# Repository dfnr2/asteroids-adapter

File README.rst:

Asteroids PCB -> Asteroids Deluxe Cabinet (and vice versa) Adapter
==================================================================

Background
----------

It is occasionally desirable to use an Asteroids PCB in an Asteroids Deluxe
cabinet (or vice versa). For example, the Braze Asteroids Multigame adapter
offers some advantages over the Asteroids Deluxe version of the multigame, such
as more accurate sound, and a Lunar Lander thruster interface. Or one may want
to use an Asteroids cabinet for testing both Asteroids and Asteroids Deluxe
PCBs. Or one may prefer the aesthetics of one cabinet, but the gameplay of the
other PCB.

The Asteroids PCB is almost compatible with the Asteroids Deluxe cabinet (and
vice versa). There are a few differences that must be addressed for an Asteroids
PCB to properly work in an Asteroids Deluxe cabinet:

#. The Deluxe cabinet uses a mirror to produce a floating 3D effect, which has the
   side effect of inverting the image along the Y axis, so Asteroids Y output needs
   to be inverted to properly work on an Asteroids Deluxe cabinet.

#. The Y-axis flip is only true for full standup cabinets. An Asteroids in an
   Asteroids Deluxe Cabaret does not require a flip.

#. The audio amplifier board in the Asteroids Deluxe PCB (A/R 1 board) has a
   voltage gain of 1, while the amplifier in the original Asteroids cabinet (A/R
   board) has a voltage gain of 10. As a result, the Asteroids PCB audio output
   is 1/10 the amplitude of the Asteroids Deluxe PCB, and will be much to quiet.
   The Asteroids audio output needs to be amplified by a factor of 10 to sound
   right.

#. Several control inputs are swapped.  These are:

   - COINL (left coin switch) and START2 (2-player START)

   - COINC (center coin switch) and START1 (1-player START)

   - ROT L (Rotate Left) and ROT R (Rotate Right)

For using an Asteroids Deluxe PCB in an Asteroids cabinet, There is a slightly
different set of considerations:

#. The Asteroids cabinet does not ground the INV_Y input of the Asteroids Deluxe
   PCB, since the Asteroids PCB has no INV_Y input. Therefore, the Y output is
   not inverted, and does not need to be re-inverted by the cabinet.

#. The Astroids Deluxe audio output amplitude will be too large, and needs to be
   divided by 10 to sound correct in an Asteroids cabinet.

#. The control inputs need to be flipped the same as for an Asteroids PCB in an
   Asteroids Cabinet.

The Adapter
-----------

.. _production_package: https://github.com/dfnr2/asteroids-adapter/tree/main/production-package/

The adapter was created with KiCad 6.0.5. KiCad was used because it is freely
available and multi-platform. The adapter design files are in the top directory.
For those who wish to produce the PCB without installing KiCad, a ZIP file is
available in the production_package_ directory.

.. image:: production-package/current_top_rendering.jpg

Assembly Notes
--------------

The PCB is designed to accomodate a variety of 44-pin edge connectors, so that almost any standard 0.156" connector will work.

- Vertical (straight) edge connectors (such as EDAC 305-044-521-202) can be
  sourced cheaply and are readily available. With a vertical connector, the
  adapter will be perpendicular to the Asteroids PCB.

- A Right-angle edge connector (such as EDAC 307-044-558-201) can be used to
  keep the adapter parallel and aligned the Asteroids PCB. These connectors are
  in production, but as far as I know are only available from EDAC, and could
  potentially be subject to supply chain issues.

Configuration
-------------

The asteroids adapter will accommodate either an Asteroids PCB in an Asteroids
Deluxe Cabinet, or an Asteroids Deluxe PCB in an Asteroids cabinet.

For Asteroids in a Deluxe cabinet, set the jumpers as follows:

- J3 (Audio gain): Asteroids in Ast Dlx Cabinet (10x gain)

- J4 (Y Flip): Flipped Y

For Asteroids Deluxe in an Asteroids cabinet, set the jumpers as follows:

- J3 (Audio gain): Ast Dlx in Asteroids Cabinet (0.1x gain)

- J4 (Y Flip): Straight Y

For Asteroids in an Asteroids Deluxe cabaret cabinet (not tested):

- J3 (Audio gain): Asteroids in Ast Dlx Cabinet (10x gain)

- J4 (Y Flip): Straight Y

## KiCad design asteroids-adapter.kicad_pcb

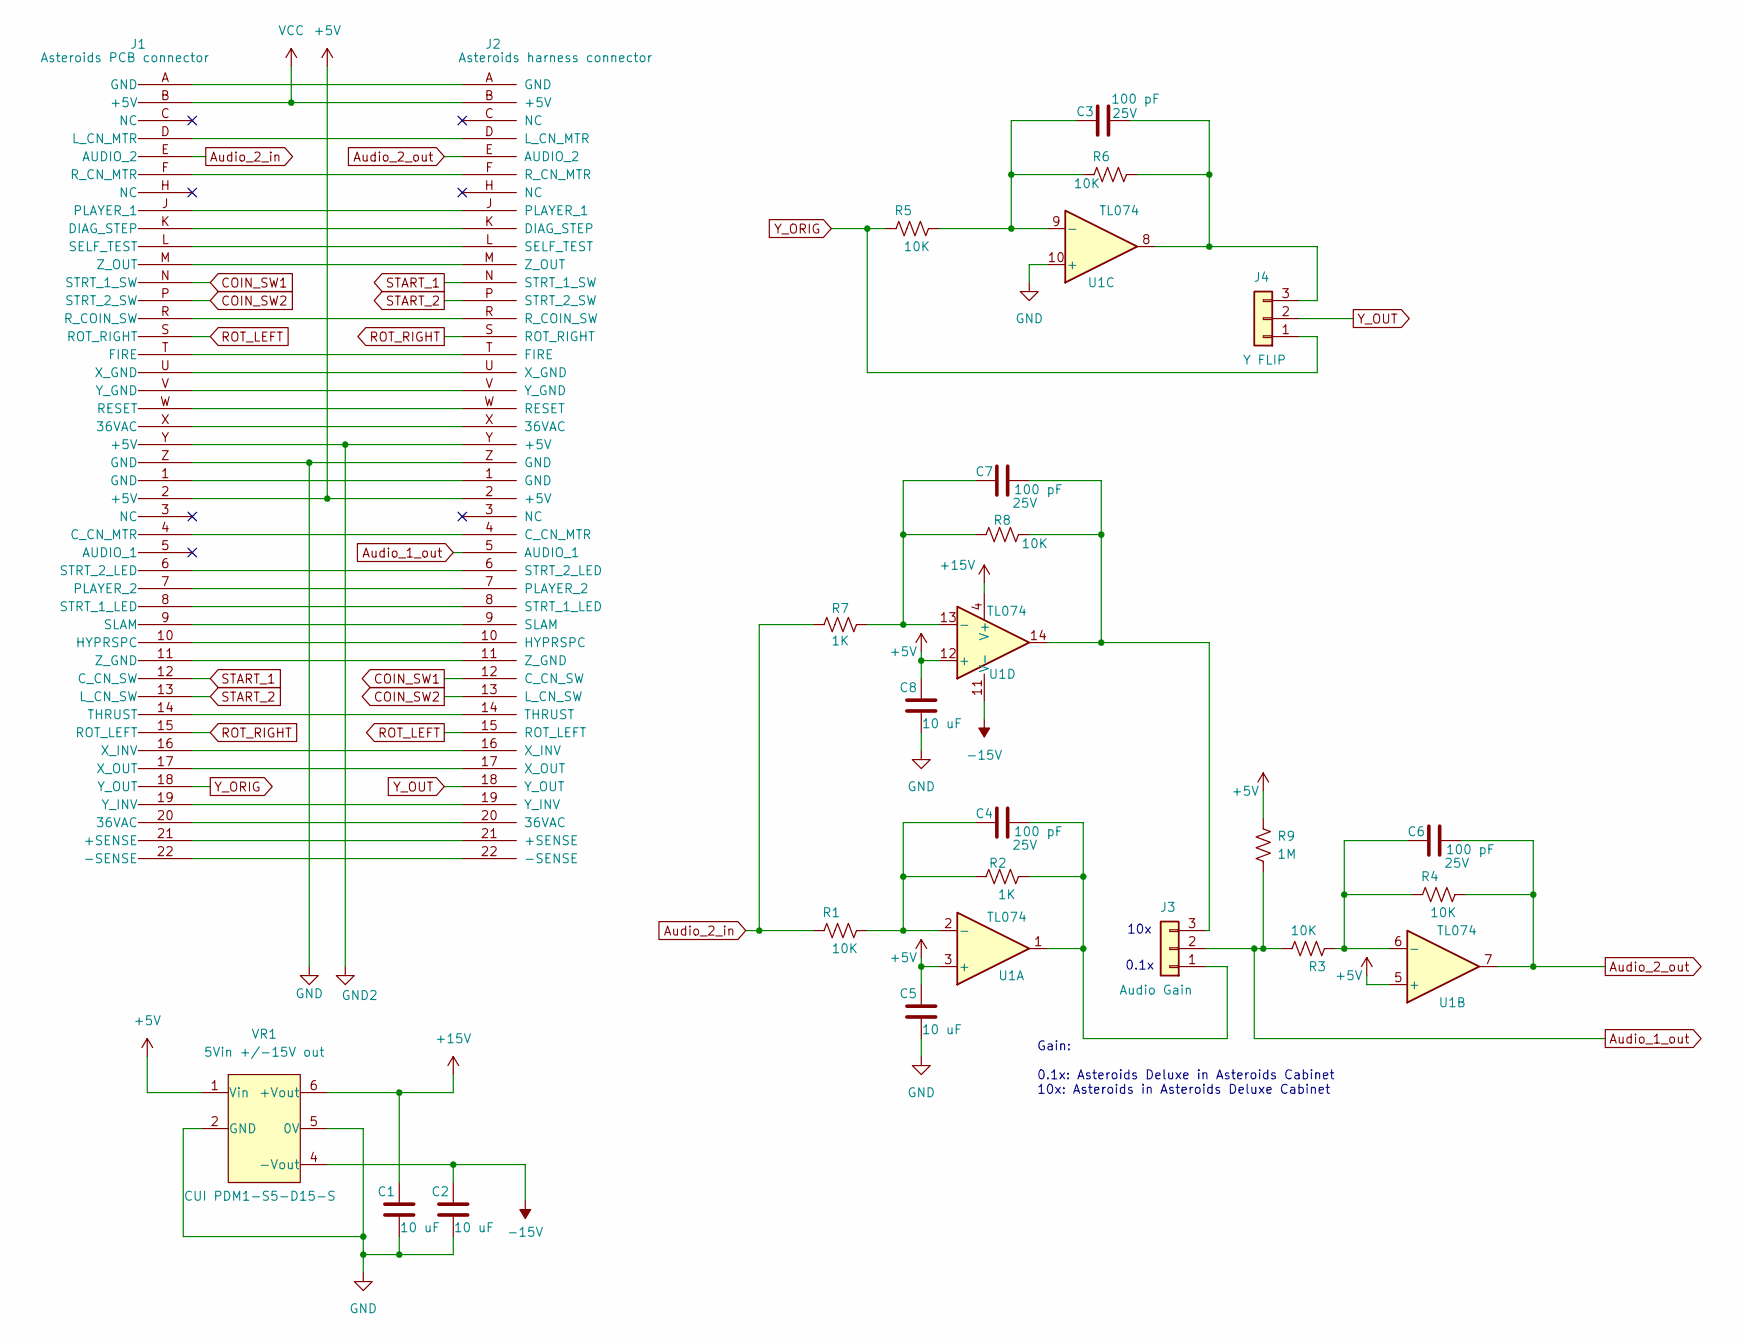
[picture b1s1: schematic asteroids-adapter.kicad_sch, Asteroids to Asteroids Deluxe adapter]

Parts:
C1, C2, C5, C8: Kemet 10 uF 25V MLCC TH; C_Disc_D3.0mm_W1.6mm_P2.50mm; Tolerance If applicable; Power Rating If applicable; Manufacturer PN C320C475K3N5TA91707301
C3, C4, C6, C7: Kemet MLCC 100 pF 5% 25V TH; C_Disc_D3.0mm_W1.6mm_P2.50mm; Tolerance 5%; Voltage Rating 25V; Manufacturer PN C315C101J3G5TA
J1: Asteroids PCB connector; EDAC 44-pin edge 0.156 universal; Tolerance n/a; Current Rating 5A; Manufacturer PN 307-044-558-201
J2: Asteroids harness connector; edge 44-pin 0.156 inch
J3: Audio Gain; PinHeader_1x03_P2.54mm_Vertical; Tolerance If applicable; Current Rating 3A; Manufacturer PN 2303-6111TG
J4: Y FLIP; PinHeader_1x03_P2.54mm_Vertical; Tolerance If applicable; Current Rating 3A; Manufacturer PN 2303-6111TG
R1, R3, R4, R5, R6, R8: Yageo 10K ohm 1% thin film TH; R_Axial_DIN0207_L6.3mm_D2.5mm_P10.16mm_Horizontal; Tolerance 1%; Power Rating 1/4 W; Manufacturer PN MFR-25FTE52-10K
R2, R7: Yageo 1K ohm 1% thin film TH; R_Axial_DIN0207_L6.3mm_D2.5mm_P10.16mm_Horizontal; Tolerance 1%; Power Rating 1/4 W; Manufacturer PN MFR-25FTE52-1K
R9: Yageo 1Mohm 1% thin film TH_1; R_Axial_DIN0207_L6.3mm_D2.5mm_P10.16mm_Horizontal; Tolerance 1%; Power Rating 1/4 W; Manufacturer PN MFR-25FTE52-1M
U1: TL074; DIP-14_W7.62mm; Tolerance If applicable; Power Rating If applicable; Manufacturer PN MFG PN
VR1: CUI PDM1-S5-D15-S; CONV_PDM1-S5-D15-S; Power Rating If applicable; Manufacturer PN PDM1-S5-D15-S

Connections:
+5V: C5.2, C8.2, J1.2 (+5V), J2.2 (+5V), R9.1, U1.3 (+), U1.5 (+), U1.12 (+), VR1.1 (Vin)
+15V: C1.2, U1.4 (V+), VR1.6 (+Vout)
-15V: C2.2, U1.11 (V-), VR1.4 (-Vout)
Audio_1_out: J2.5 (AUDIO_1), J3.2, R3.1, R9.2
Audio_2_in: J1.E (AUDIO_2), R1.2, R7.1
Audio_2_out: C6.2, J2.E (AUDIO_2), R4.1, U1.7
COIN_SW1: J1.N (STRT_1_SW), J2.12 (C_CN_SW)
COIN_SW2: J1.P (STRT_2_SW), J2.13 (L_CN_SW)
GND: C1.1, C2.1, C5.1, C8.1, J1.Z (GND), J2.Z (GND), U1.10 (+), VR1.2 (GND), VR1.5 (0V)
GND2: J1.Y (+5V), J2.Y (+5V)
unnamed: C3.1, R5.1, R6.2, U1.9 (-)
unnamed: C3.2, J4.3, R6.1, U1.8
unnamed: C4.1, R1.1, R2.2, U1.2 (-)
unnamed: C4.2, J3.1, R2.1, U1.1
unnamed: C6.1, R3.2, R4.2, U1.6 (-)
unnamed: C7.1, R7.2, R8.1, U1.13 (-)
unnamed: C7.2, J3.3, R8.2, U1.14
unnamed: J1.1 (GND), J2.1 (GND)
unnamed: J1.4 (C_CN_MTR), J2.4 (C_CN_MTR)
unnamed: J1.6 (STRT_2_LED), J2.6 (STRT_2_LED)
unnamed: J1.7 (PLAYER_2), J2.7 (PLAYER_2)
unnamed: J1.8 (STRT_1_LED), J2.8 (STRT_1_LED)
unnamed: J1.9 (SLAM), J2.9 (SLAM)
unnamed: J1.10 (HYPRSPC), J2.10 (HYPRSPC)
unnamed: J1.11 (Z_GND), J2.11 (Z_GND)
unnamed: J1.14 (THRUST), J2.14 (THRUST)
unnamed: J1.16 (X_INV), J2.16 (X_INV)
unnamed: J1.17 (X_OUT), J2.17 (X_OUT)
unnamed: J1.19 (Y_INV), J2.19 (Y_INV)
unnamed: J1.20 (36VAC), J2.20 (36VAC)
unnamed: J1.21 (+SENSE), J2.21 (+SENSE)
unnamed: J1.22 (-SENSE), J2.22 (-SENSE)
unnamed: J1.A (GND), J2.A (GND)
unnamed: J1.D (L_CN_MTR), J2.D (L_CN_MTR)
unnamed: J1.F (R_CN_MTR), J2.F (R_CN_MTR)
unnamed: J1.J (PLAYER_1), J2.J (PLAYER_1)
unnamed: J1.K (DIAG_STEP), J2.K (DIAG_STEP)
unnamed: J1.L (SELF_TEST), J2.L (SELF_TEST)
unnamed: J1.M (Z_OUT), J2.M (Z_OUT)
unnamed: J1.R (R_COIN_SW~), J2.R (R_COIN_SW~)
unnamed: J1.T (FIRE), J2.T (FIRE)
unnamed: J1.U (X_GND), J2.U (X_GND)
unnamed: J1.V (Y_GND), J2.V (Y_GND)
unnamed: J1.W (RESET), J2.W (RESET)
unnamed: J1.X (36VAC), J2.X (36VAC)
ROT_LEFT: J1.S (ROT_RIGHT), J2.15 (ROT_LEFT)
ROT_RIGHT: J1.15 (ROT_LEFT), J2.S (ROT_RIGHT)
START_1: J1.12 (C_CN_SW), J2.N (STRT_1_SW)
START_2: J1.13 (L_CN_SW), J2.P (STRT_2_SW)
VCC: J1.B (+5V), J2.B (+5V)
Y_ORIG: J1.18 (Y_OUT), J4.1, R5.2
Y_OUT: J2.18 (Y_OUT), J4.2

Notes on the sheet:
0.1x
10x
Gain: 0.1x: Asteroids Deluxe in Asteroids Cabinet 10x: Asteroids in Asteroids Deluxe Cabinet

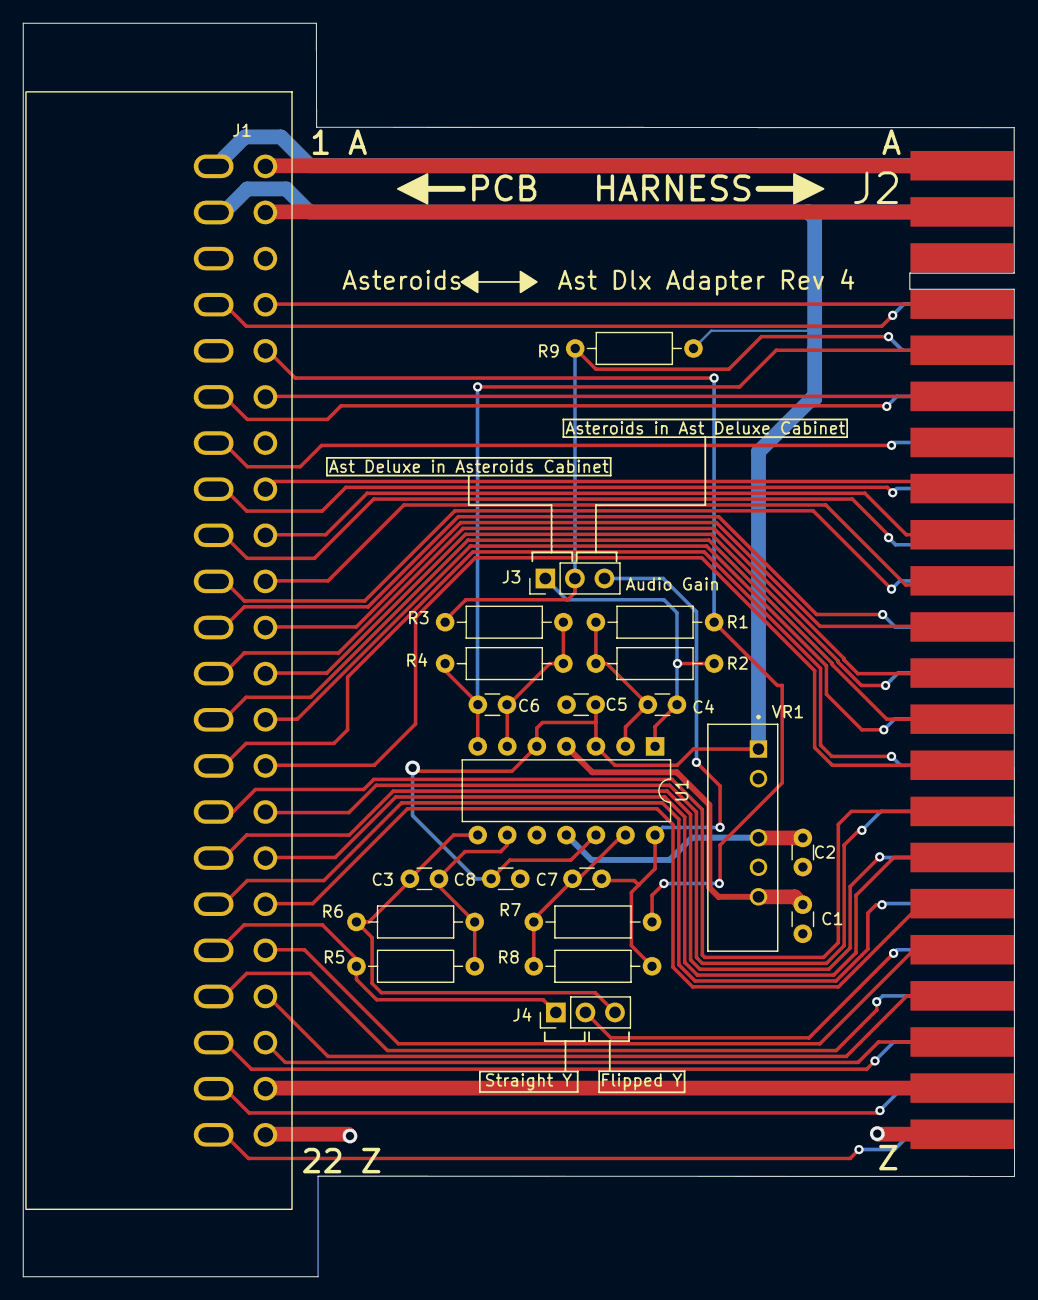
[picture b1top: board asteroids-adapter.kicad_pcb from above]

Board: 2 copper layers, 85.2 x 107.7 mm, 23 parts (0 on the bottom side), 52 nets.

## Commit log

2022-02-21 Rev 1 of Asteroids PCB -> Ast Deluxe Cab adapter
2022-02-21 Fixed DC-DC footprint and silk screen info
    - Downloaded from CUI website
    - fixed connector labels
2022-02-21 Make sure all the caps have library symbols
2022-02-21 Replace SMT DC/DC converter with Through-hole Part
    Retro hobbyists prefer through hole.
2022-02-21 Add part number to DC DC converter
2022-02-22 No solder mask around the edge connectors.
    - Original footprint had wrong solder mask layer for bottom layer pads.
    Fixed, and also place solder mask keepout over entire length of the
    edge connectors
    - Trimmed ground pour to prevent "fingers" extending between edge
    connector pads.
2022-02-24 Power and GND to DC-DC converter were swapped
    Fixed by swapping the power and ground connections to pins 1 and 2 of
    the DC-DC converter.
2022-02-24 Track went between edge connectors
    Moved track off of edge connector region.
2022-02-24 widen no-soldermask zone around edge connectors
    - widened the f-mask and b-mask rectangles in footprint
    - updated footprints in PCB
    - moved some pads outside of no-mask zones
2022-02-24 Add bypass to 5V op-amp reference
    - Added 10 uf cap at (+) input of both audio inverter op amps, to reduce
    noise.
2022-03-08 Move parts for narrower design
    - Still need to move connector and finish re-routing
2022-03-08 squashed PCB
    Still need to clean up PCB outline and re-route
2022-03-09 Completed routing on compact PCB
2022-03-09 Rearranged config silk screen table
    - easier to understand row format.
    - white boxes to mark selected configuration.
2022-03-14 Swith to PCB-mount edge connector
    This is easier to assemble and provides a more reliable connection, due
    to reduced likelyhood of distorting the edge connector position.
2022-03-14 Added connections for X_INV and Y_INV
2022-03-14 Add jumper for configuration
    Configure unused opamp as 0.1x gain, and add jumper to select between
    10x and 0.1x gain audio.
2022-03-15 Fixed jumper to 0.1" 3-pin header
    also silk screen fixed
2022-05-14 Fixed audio output selection
    Audio 1 was always connected to the x10 gain amplifier, instead of the
    gain selected by the jumper.
    Also, fixed the 3-pin header in the schematic to use the correct 2.54mm
    pitch part.
2022-05-15 Universal connector
    Update connector footprint to accommodate 0.2 and 0.156 row spacing, and
    vertical or right-angle connectors.
    Update more parts with full parameters
    Add 1M resistor to pin 2 of jumper, so op-amp input isn't floating if
    jumper is left out.
2022-05-15 Added library item for 3-pin connector
    Need full params for all items to make a BOM.
2022-05-16 Clean up Makefiles and BOM generation
    - Makefiles auto-generate README files
    - Fix part parameters and BOM configuration
2022-05-19 Updated component fields in PCB
2022-05-19 Generate RST README files.
    - Include Makefile target to generate PDF using pandoc
2022-05-19 Update Makefiles to specify RST or PDF README
2022-05-20 More README file cleanups
2022-05-20 Added FLIP Y jumper
    FLIP Y provides required for AST Deluxe in AST cab, and also for
    Asteroids in a Deluxe cabaret cabinet.
    Added 2-pin header to library
    More makefile tweaks.
2022-05-21 More cleanups and bump version
    - Cleaned up schematic to align components to grid
    - Added bypass cap on 0.1x gain input
    - More Makefile cleanups
2022-05-30 Updated production package Makefiles
2022-05-30 Fixes for Dlx in Ast cabinet
    - Fixed reversed opamp inputs to the 0.1x gain audio path
    - Changed the implementation of the "Y flip" jumper. Now the jumper
    selects the original signal or the reversed signal, rather than
    grounding the "INV_Y" line. This results in a more predictable result.
    I.e., Moving the jumper will always flip the Y axis, while a jumper that
    grounds "INV_Y" will have no effect if the line is grounded elsewhere in
2022-05-30 Added final production package for convenience
2022-05-30 Add top rendering from production package
    - Used by top-level repo README file
2022-05-30 Updated README and Makefile
    - README includes a Makefile-generated link to the PCB rendering,
    instead of hard-coding the filename in the README, since the name
    changes with the revision number.
    Add link to rendering
    Replace link to rendering with a copy
    README uses version-independent link to image
2022-06-11 Swapped amplifier gains in schem to match pcb
    - In Rev 4, the PCB silk screen reversed the labels for J3, "Asteroids in
    Ast Deluxe Cabinet" and "Ast Deluxe in Asteroids Cabinet". Since some
    PCBs were already made, the solution is to swap the resistor values in
    the schematic to make the J3 labels correct, so no PCB change is needed
    and no respin required.
    - Bump the schematic rev to 4.1. PCB remains at rev 4
